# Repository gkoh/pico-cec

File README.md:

# Pico-CEC

A Raspberry Pi Pico based project to bridge HDMI CEC (Consumer Electronics
Control) and USB HID keyboard control (especially for use with Kodi).

## Update January 2026

The reference hardware for `pico-cec` has been upgraded from RP2040 to RP2350. Support for RP2040 builds will continue where possible.

## Motivation

Micro/mini desktops are plentiful as second hand, budget friendly media players,
especially when installed with Kodi (eg. LibreELEC).
However, many of these devices do not support HDMI-CEC and require the user to
use additional peripherals (eg. wireless keyboard, game controller).

In this project we use a Pico to both:
* handle the CEC protocol on the HDMI port
* adapt the user control messages into USB keyboard inputs

## What Works
* HDMI CEC frame send and receive
* EDID parsing to determine HDMI physical address
* LibreELEC recognises Pico-CEC as an USB HID keyboard
* HDMI CEC basic user control messages are properly mapped to Kodi shortcuts,
  including:
   * navigations arrows
   * select
   * back
   * play
   * pause
   * numbers 0-9
 
> [!CAUTION]
> The build quality of the HDMI breakout boards is highly variable, thus pass through of 4K video may not function in all circumstances.

## Cloning
To avoid cloning unneeded code, clone like this:
```
git -c submodule.active="lib/tinyusb" -c submodule.active=":(exclude,glob){lib,hw}/*" clone --recurse-submodules
```

Alternatively, clone everything in pico-sdk and tinyUSB:
```
git clone --recurse-submodules
```

## Building
This project uses the 'normal' CMake based build.  
The build depends on cmake (obviously), gcc-arm-none-eabi, and libnewlib-dev.

Two boards are supported, and the RP2040 and RP2350 produce incompatible
`.uf2` images, so build for the board you actually have:
```
$ git clone <blah blah as above>
$ cd pico-cec
```

For the Seeed XIAO RP2350 (current reference hardware):
```
$ cmake -S . -B build -DPICO_BOARD=seeed_xiao_rp2350 && cmake --build build
```

For the Seeed XIAO RP2040 (legacy):
```
$ cmake -S . -B build -DPICO_BOARD=seeed_xiao_rp2040 && cmake --build build
```

Switching boards requires a clean build directory (`rm -rf build`).

### Customising the Build
The CMake project supports three options:
* PICO_BOARD: specify variant of Pico board, defaults to Seeed XIAO RP2350 (potential values [here](https://github.com/raspberrypi/pico-sdk/tree/master/src/boards/include/boards))
* CEC_PIN: specify GPIO pin for HDMI CEC, defaults to GPIO3
* CEC_OSD_NAME: specify the OSD string for HDMI input Pico-CEC is controlling, defaults to "Pico-CEC"
Example invocation to specify:
* use Raspberry Pi Pico development board
* use GPIO pin 11
* use OSD_NAME "Bazzite"

```
$ cmake -DPICO_BOARD=pico -DCEC_PIN=11 -DCEC_OSD_NAME="Bazzite" ..
$ make
```

## Installing
Assuming a successful build, the build directory will contain `pico-cec.uf2`,
this can be written to the Pico as per normal:
* connect the Pico to computer via USB cable
* reset the Pico by holding 'Boot' and pressing 'Reset'
   * Pico now presents as a USB mass storage device
* copy `pico-cec.uf2` to the Pico
* disconnect

A command line interface over serial port is available, the guide can be found
here: [Command Line Interface Guide](https://github.com/gkoh/pico-cec/wiki/Command-Line-Interface-Guide)

## Blinking Lights
The RGB LED provides basic functional diagnosis:
* blue 2Hz: idle, CEC standby
* green 2Hz: CEC active
* green flash: CEC user button pressed
* red: crash

If there are no lights, something is very wrong.
If this occurs, please consider raising an issue.

# Real World Usage
This is currently working with:
* a Sharp 60" TV (physical address 0x1000)
   * directly connected to TV HDMI input 1
* through a Denon AVR connected to the Sharp TV (physical address 0x1100)
   * Pico-CEC connected to Denon AVR HDMI input 1
   * Denon AVR connected to TV HDMI input 1
* a Sony 60" TV (physical address 0x1000)
   * directly connected to TV HDMI input 1

# Design
## Hardware
The hardware connections are extremely simple. Both HDMI CEC and the Pico are
3.3V obviating the need for level shifters. The DDC bus (for EDID) is I2C and
5V, however, the Pico appears to be 5V tolerant.

Additionally, we rely on the GPIO input/output impedance states to read or drive
the CEC bus. DDC is I2C requiring data and clock lines.
Thus, we need to directly connect four wires:
* HDMI CEC pin 13 direct to a GPIO
* HDMI CEC ground pin 17 direct to GND
* HDMI DDC clock pin 15 direct to SCL
* HDMI DDC data pin 16 direct to SDA
* Optional if safe:
   * HDMI +5V power pin direct to 5V

For the Seeed Studio XIAO RP2350:
* HDMI pin 13 --> D10
* HDMI pin 17 --> GND
* HDMI pin 15 --> D5
* HDMI pin 16 --> D4
* HDMI pin 18 --> 5V/VUSB

### Schematic

After this we:
* connect `Pico-CEC` to the HDMI output of the PC
* connect the HDMI cable from the TV to `Pico-CEC`
* connect a USB cable from `Pico-CEC` to the PC

### Prototype

### Enclosure
The enclosure is a reasonably simple three piece sandwich 3d print modelled with OpenSCAD. It is designed to be printed as three separate pieces which are bolted together with M3 nuts and bolts.
An exploded preview of the result can be found in this [STL](openscad/pico-cec.stl).

### PCB

The hardware is split across two KiCad projects under [`pcb/`](pcb). You will
need to have *both* these boards produced:

* [`pcb/hdmi-breakout`](pcb/hdmi-breakout) — the HDMI passthrough breakout that
  carries the CEC and DDC signals. This is a 4-layer board; order it with the
  **JLC04161H-7628 stackup**. Stackup is not a minor detail; incorrect stackup
  will destroy performance.
* [`pcb/rp2040-adaptor`](pcb/rp2040-adaptor) — a simple breakout for the RP2040-Zero
  that connects to the HDMI breakout. This is an ordinary **2-layer** board with
  no controlled-impedance requirement, so any standard stackup is fine.

Shared symbols and footprints live in [`pcb/library`](pcb/library). Fabrication
outputs (gerbers, BOM, CPL) for each board can be generated with
[`jlcpcb_fab.py`](jlcpcb_fab.py).

Additional BOM (parts to source separately on top of the fabricated boards):

| Count | Part |
| ----- | ---- |
| 2 | HDMI Type-A receptacle (Molex 208658-1001, LCSC C138388) |
| 1 | Waveshare RP2040-Zero |
| 2 | 1×9 2.54mm male pin header strip |
| 2 | 1×9 2.54mm female header / socket strip |
| 2 | M3 × 16mm socket head cap screw |
| 2 | M3 nut |

Remember that you can easily cut a longer 2.54mm header to size with some snips.

### Assembly

## Software
The software is extremely simple and built on FreeRTOS tasks:
* cec_task
   * interact with HDMI CEC sending user control message inputs to a queue
* hid_task
   * read the user control messages from the queue and send to the USB task
* usbd_task
   * generate an HID keyboard input for the USB host
* blink_task
   * heart beat, no blink == no work

## cec_task
The CEC task comprises three major components:
* `cec_frame_recv`
   * receives and validates CEC packets from the CEC GPIO pin
   * edge interrupt driven state machine
      * rewritten from busy wait loop to reduce CPU load
* `cec_frame_send`
   * formats and sends CEC packets on the CEC GPIO pin
   * alarm interrupt driven state machine
      * rewritten from busy wait loop to reduce CPU load
* main control loop
   * manages CEC send and receive

All the HDMI frame handling was rewritten to be hardware/timer interrupt driven
to meet real-time constraints.
Attempts to increase the FreeRTOS tick timer along with busy wait loops were
simply unable to consistently meet the CEC timing windows.

## hid_task and usbd_task

These are simple FreeRTOS tasks effectively taken straight from the TinyUSB
examples.

## Dependencies
This project uses:
* [crc](https://github.com/gityf/crc)
* [FreeRTOS-Kernel](https://github.com/FreeRTOS/FreeRTOS-Kernel)
* [pico-sdk](https://github.com/raspberrypi/pico-sdk)
   * [tinyusb](https://github.com/hathach/tinyusb)
* [tcli](https://github.com/dpse/tcli)

# Hardware
* Seeed Studio XIAO RP2350 (chosen for form factor)
   * https://www.seeedstudio.com/Seeed-XIAO-RP2350-p-5944.html
   * Originally prototyped on the Raspberry Pi Pico board (still works but
     requires RGB unhacking)
* HDMI male/female passthrough adapter
   * Listed as 'HDMI Male and Female Test Board MINI Connector with Board PCB
     2.54mm pitch 19/20pin DP HD A Female To Male Adapter Board'
   * Model number: WP-905
   * https://www.aliexpress.com/item/1005004791079117.html
* custom 3d printed housing

# Bill of Materials
| Component | Quantity | Price (January 2026) (AUD) |
| :--- | ---: | ---: |
| Seeed Studio XIAO RP2350 | 1 | 10.60 |
| HDMI male/female adapter | 1 | 4.30 |
| M3x10mm bolt & nut | 2 | 0.16 |
| M3x20mm bolt & nut | 2 | 0.17 |
| Random short wires | 4 | basically free |
| Scunge 3D print from friend | 1 | mostly free |
| Umpteen hours of engineering | 1 | priceless |
| Total | | 15.23 |

# cec-compliance
As of v0.2.2, `pico-cec` now passes the cec-compliance test suite found in the
Linux `v4l-utils` package.
More details can be found in the wiki entry:
https://github.com/gkoh/pico-cec/wiki/CEC-Compliance-Testing

Furthermore, `pico-cec` has been able to survive one hour of cec-compliance fuzz
testing.

# Debugging
A command line terminal over serial port is supported.
Details can be found in the wiki entry:
https://github.com/gkoh/pico-cec/wiki/Command-Line-Interface-Guide

In particular, `debug on` will log all CEC traffic to the terminal.

# Future
* implement CEC send and receive in PIO
* port to ESP32?
   * WS2812 driver will need platform support, perhaps to RMT
   * implement CEC in RMT

# References
Inspiration and/or ground work was obtained from the following:
* https://github.com/SzymonSlupik/CEC-Tiny-Pro
* https://github.com/tsowell/avr-hdmi-cec-volume

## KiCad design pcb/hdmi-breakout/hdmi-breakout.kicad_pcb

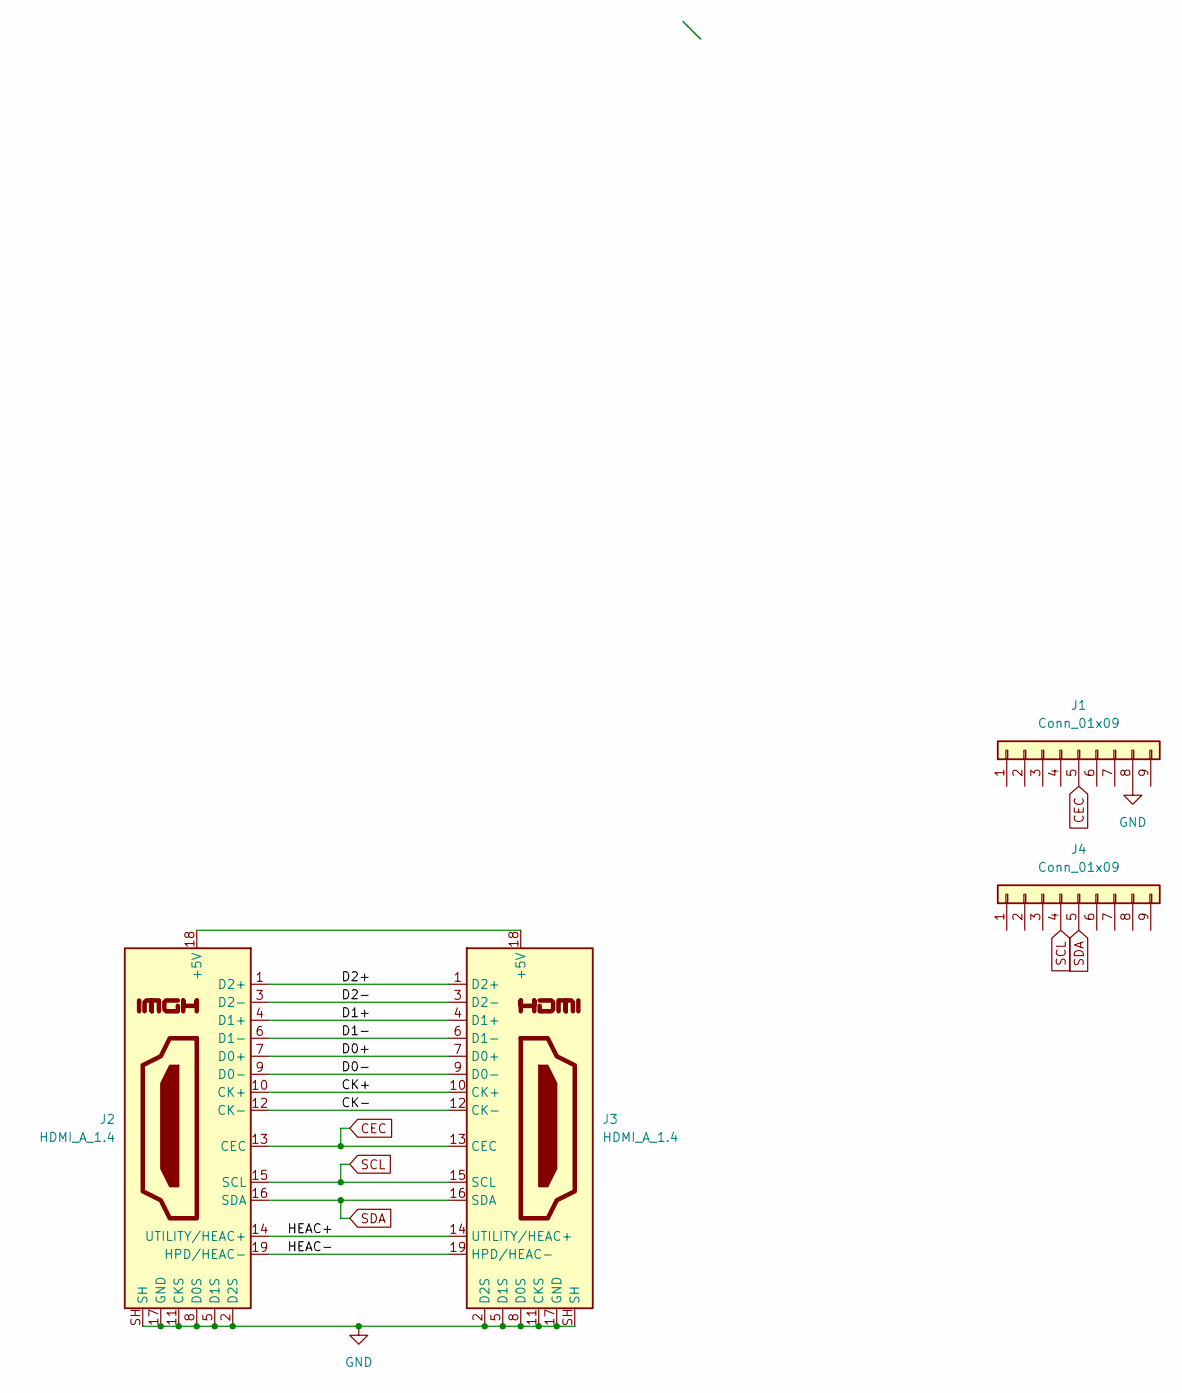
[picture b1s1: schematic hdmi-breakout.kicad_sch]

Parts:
J1, J4: Conn_01x09; PinHeader_1x09_P2.54mm_Vertical
J2, J3: HDMI_A_1.4; HDMI_A_Molex_208658-1001_Horizontal; LCSC C138388

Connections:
/CK+: J2.10 (CK+), J3.10 (CK+)
/CK-: J2.12 (CK-), J3.12 (CK-)
/D0+: J2.7 (D0+), J3.7 (D0+)
/D0-: J2.9 (D0-), J3.9 (D0-)
/D1+: J2.4 (D1+), J3.4 (D1+)
/D1-: J2.6 (D1-), J3.6 (D1-)
/D2+: J2.1 (D2+), J3.1 (D2+)
/D2-: J2.3 (D2-), J3.3 (D2-)
/HEAC+: J2.14 (UTILITY/HEAC+), J3.14 (UTILITY/HEAC+)
/HEAC-: J2.19 (HPD/HEAC-), J3.19 (HPD/HEAC-)
CEC: J1.5, J2.13 (CEC), J3.13 (CEC)
GND: J1.8, J2.2 (D2S), J2.5 (D1S), J2.8 (D0S), J2.11 (CKS), J2.17 (GND), J2.SH, J3.2 (D2S), J3.5 (D1S), J3.8 (D0S), J3.11 (CKS), J3.17 (GND), J3.SH
unnamed: J2.18 (+5V), J3.18 (+5V)
SCL: J2.15 (SCL), J3.15 (SCL), J4.4
SDA: J2.16 (SDA), J3.16 (SDA), J4.5

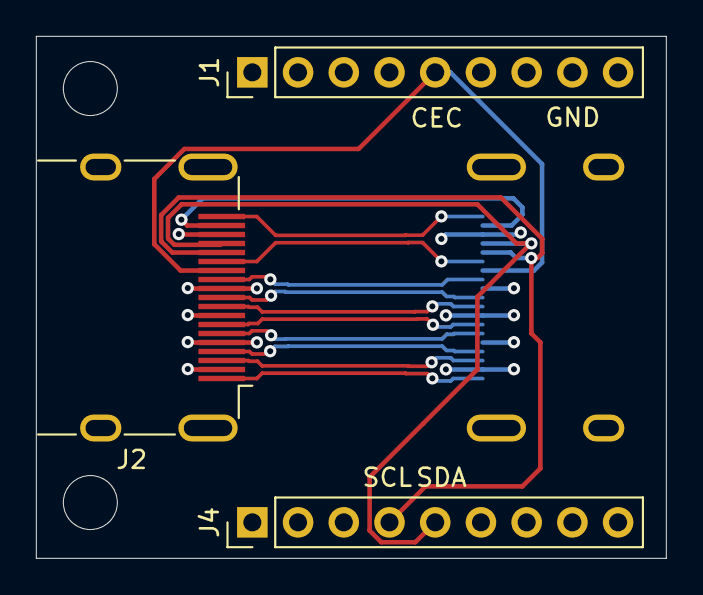
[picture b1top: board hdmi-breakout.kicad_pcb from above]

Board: 4 copper layers, 35.0 x 29.0 mm, 4 parts (1 on the bottom side), 15 nets.

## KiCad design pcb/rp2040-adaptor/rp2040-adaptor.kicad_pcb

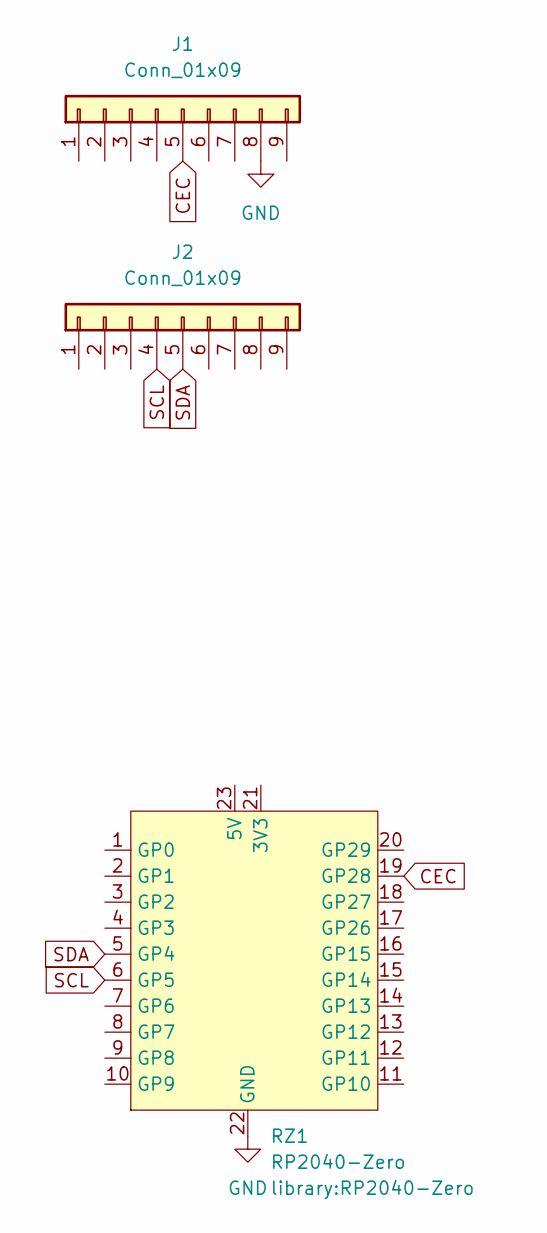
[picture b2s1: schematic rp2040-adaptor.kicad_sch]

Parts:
J1, J2: Conn_01x09; PinSocket_1x09_P2.54mm_Vertical
RZ1: RP2040-Zero

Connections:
CEC: J1.5, RZ1.19 (GP28)
GND: J1.8, RZ1.22 (GND)
SCL: J2.4, RZ1.6 (GP5)
SDA: J2.5, RZ1.5 (GP4)

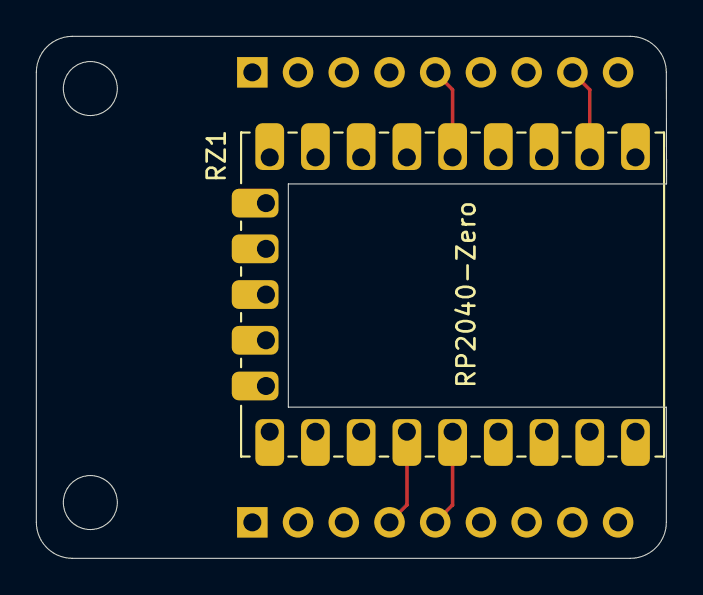
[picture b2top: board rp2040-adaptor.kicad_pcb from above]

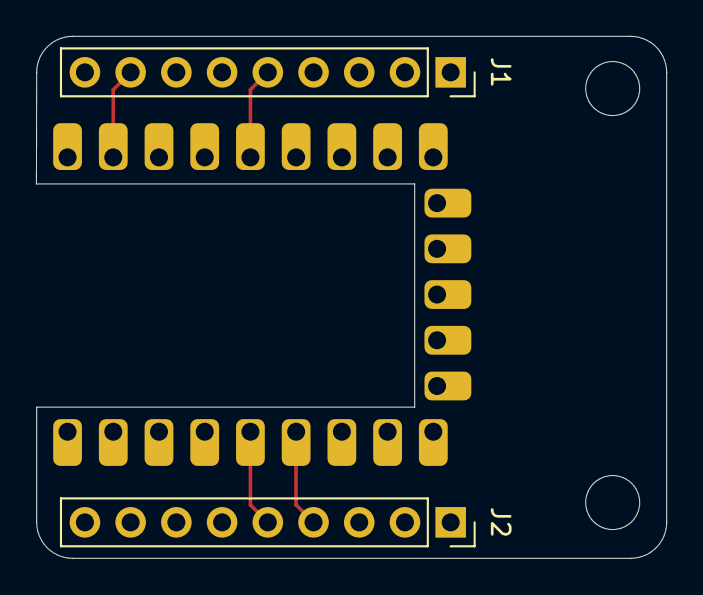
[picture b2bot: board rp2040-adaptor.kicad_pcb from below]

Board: 2 copper layers, 35.0 x 29.0 mm, 3 parts (2 on the bottom side), 4 nets.

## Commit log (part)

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2024-05-28 Initial commit.
2024-06-01 Fix stack sizes for tasks.
    FreeRTOS stack sizes are specified as words (default 4 bytes for
    rp2040).
    This may have been the cause of the intermittent hangs.
2024-06-04 Another attempt to avoid random hang.
    Tweak stack sizes again.
    Give usbd all 4k stack on core 1.
    Move HID to core 0.
    Disable copy_to_ram for now.
2024-06-07 Tweak various parameters.
    Send notify on abort (otherwise aborted CEC messages hang the system).
    Add necessary PICO_SYNC definitons to ensure FreeRTOS compatibility.
    This version seems to have fixed the various hangs.
    (Retweak the stack sizes based on high water mark values).
2024-06-10 Tweak 3d model after prototype print.
    Increase various tolerances and add LED visibility.
    Also fix dependency in Makefile.
2024-06-10 Freeze FreeRTOS-Kernel at V11.1.0.
    pico-sdk is already frozen at 1.5.1.
2024-06-16 Further cleanup of CMake project file.
2024-06-19 Initial cut of README.
2024-06-19 Tweak case tolerances.
    Increase M3 nut radius.
    Increase M3 bolt radius.
    Increase HDMI male width.
2024-06-19 Add build directory to gitignore.
2024-06-23 Add clang-format check to CI.
    Add recursive submodule checkout fix.
2024-06-23 Fix more silly mistakes.
2024-06-23 Add submodule init & update for tinyusb.
2024-06-23 Add anonymous scope to fix declaration compiler error.
    Seems an older version of GCC and/or C standard doesn't like it.
2024-06-23 Add STL export step to CI.
2024-06-23 Add required runs-on.
2024-06-23 Flatten the download-artifact assets.
2024-06-23 Give release job write permission to upload assets.
2024-07-01 Fix README.md table.
2024-07-03 Adjust semi-exploded for piece clarity.
2024-07-03 Fix typo.
2024-07-21 Implement logical address allocation for playback addresses.
    With an array of the playback addresses, ping each one in order to
    discover which is free.
    Whilst here, implement the CEC version reply (and reply with 1.3a).
2024-07-22 Update real-world usage in README.
2024-07-25 Implement EDID parsing to query physical address.
    Add I2C support for the HDMI DDC bus and query the upstream device for
    our HDMI physical address.
    This means the physical address is no longer hardcoded.
    Tested working with the following upstream devices:
    * Sharp TV
    * Sony TV
2024-07-27 Clean up FreeRTOS config header.
2024-07-28 Refactor for CEC message handling.
2024-07-28 Issue a reset before reading.
    Looks like we should reset the DDC/EDID state before attempting a read.
    Do this by writing a 0 to the EDID address before trying to read any
    data back.
2024-07-28 Fix support for Samsung TV. (#6)
    * Clean up FreeRTOS config header.
    * Add debug target.
    The debug target removes the USB HID binding and allows the Pico to send
    serial output to USB.
    NB. This build output tends to hang randomly, a lot, use at risk.
    * Refactor for CEC message handling.
2024-07-29 Update schematic.
    Correct the schematic wiring pin for CEC.
2024-08-10 Add future point to README
    Perhaps port to ESP32?
    Would only really need to refactor the HDMI tx/rx interrupt/timer handling.
    Everything else is reasonably hardware agnostic.
2024-08-18 Added mappings for subtitle and context menu. (#10)
    * Added mappings for subtitle and context menu.
    * Run clang-format.
    ---------
2024-09-09 Correct workflow variable substitution.
    Also remove stale include path.
2024-09-10 Initial support for USB composite device HID and CDC. (#13)
    * Initial support for USB composite device HID and CDC.
    Enable CDC so Pico-CEC appears as a connectable serial TTY device with
    baud rate 115200.
    Add tcli v0.2.5 as submodule.
    Add basic example CLI support via tcli for:
    * reboot [bootsel]
2025-02-15 Stop installing recommended packages for CI.
    Seriously, we don't need all that.
2025-02-15 Add another missing package.
2025-02-15 Add non-volatile configuration parameters.
    Increase NVS block to 64kB.
    Import CRC library.
    Add default EDID probe delay.
    Add default physical address (0x0000 means EDID probe).
    Add default Kodi keymap.
2025-02-19 Add delay to avoid serial output lock.
    Serial still causes full system hang sometimes, but this seems to make
    it occur far less often.
2025-02-19 Add link to CLI wiki.
2025-02-19 Disable SMP.
    CPU stats indicate pico-cec idles both cores almost 100% of the time.
    This means CPU requirements are insanely low, as expected.
    Now we just mostly idle a single core.
    This is also seems to completely eliminate the serial deadlock
    behaviour.
    (Updating to pico-sdk v2.1.1 did not fix it).
2025-02-22 Pass cec-compliance `--test-core`.
2025-02-22 Pass cec-compliance routing test.
2025-02-23 Improve some debug output traces.
    Condense the EDID query block logging by printing 8 bytes at a time.
    Modify the CEC message direction log such that:
    * "x -> y" = x sent to y with ack
    * "x <- y" = y sent to x with ack
    * "x ~> y" = x sent to y no ack
    * "x <~ y" = y sent to x no ack
2025-02-26 Properly support default keymap upgrades.
    Implement NVS version detection and migration.
    Add a 'keymap_type' field for identification of keymaps.
    Add currently unused 'logical address' configuration.
    Add keymap for MiSTer and provide build time support to enable.
    Refactor keymap handling.
    Add 'show nvs' command to display basic NVS configuration.
2025-02-26 Add unused device type.
2025-02-27 Fix build for boards with no user LED.
    Update README to clarify Pico dev board support.
2025-02-28 Fix user control message handling.
    Ensure that pico-cec only responds to user control messages destined for
    its logical address.
    Prior to this fix, pico-cec would respond to _all_ user control messages
    on the CEC bus, regardless of destination device.
2025-02-28 Add github run-id to artifact reference.
2025-02-28 Add some missing undecoded CEC message IDs.
2025-03-03 Improve active source handling.
    If `Request Active Source` is received three times without a response
    from any other device, become the active source.
2025-03-04 Update README.md
    Correct the wire count in the BOM.
    Add more future things.
2025-06-13 Improve code portability
    Minor additions/modifications required to existing code-base for compatibility with espressif esp32 compiler.
2025-06-15 Added console support on secondary UART
    The secondary esp32 uart is configured for the tcli console, with the primary uart still utilised for diagnostics.
2025-06-17 rename a couple of port support modules
    In order to improve namespace clarity utilised git mv to change name of a couple of port support modules.
2025-06-18 Update hdmi-cec-link.h
    Remove draft commit summary from source file.
2025-06-19 Correct header inclusion for 'memset()'.
2025-06-19 Update hdmi-cec-link.c
    Fix a missed clang-format violation.
2025-06-23 esp32 target now sends and receives cec messages
    Significant progress along with major cleanup of the port code.
    Also successfully build tested the pico target. Requires replacing CMakeFiles.txt with the accompanying CMakeFiles.pico
    More work to come with renaming a few modules as discussed in the refactoring pull request.
2025-06-24 Further fix-ups to previous commit
    Mostly to quiet the format checker, but a few fixes addressing issues found during an independent build test.
2025-06-24 Exclude `lib` from clang-format.
2025-06-26 Add i2c support and improve trace capability
    Both the legacy and new esp-idf i2c driver models are optionally supported. The former requires no change to the mainline source, the later requires a single processor conditional.
2025-07-01 Rename select modules and numerous update candidates
    Significant cleanup preparing for a merge candidate.
    As yet no run-time test conducted on pico hardware.
    Proposed solution to disparate requirements for CMakeLists.txt is to require the user to copy one of the template versions as provided.
    Now includes I2C (DDC) support, with options to try both new and legacy esp-idf i2c drivers.
    Two potential methods to facilitate pico-sdk header inclusion - either with dummy (empty) headers in a replicated directory structure (to satisfy the C pre-processor), or by including all required he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
2025-07-01 Appease clang-format
2025-07-06 progress towards decoupling cec and cdc functionality, et-al
    decouple cec user control name strings from both config and log modules
    - allows cec-log to exist independent of the application configuration (cec-config) functionality
    - cec-log could readily be minimised to not support higher level cec user control specific support
    - cec-config need know nothing else about the cec logging capability (this may warrant a re-think)
    - cec-config just needs access to a string table which it doesn't make sense to own
    move and rename function cec_get_uptime_ms() to cec_log_uptime_ms()
2025-07-13 Refactor _CDC_BR handling.
    Add _LOG_BR macro for _CDC_BR to streamline header inclusion.
    Any modules requiring logging need only include `cec-log.h`.
2025-07-18 Update cec-log.h
    Attempt to address the failing GitHub automated build tests.
2025-07-18 Isolate pico-sdk specific header files
    Isolation of pico-sdk only include files from architecture independent common source modules is required to support ports to other devices.
2025-07-24 Update on esp32 port progress
    Builds and runs nicely on both esp32 and pico-pi.
    With the addition of several new diagnostic features, RX_ABORTS have seemingly been eliminated.
    Additional feature allows asynchronous sending of cec messages from external tasks.
2025-07-24 Grin and bear the frustration that is Git
2025-08-19 Progress update
2025-08-19 Address the format checker issue
2025-12-26 Add CEC-Enabler board definiton from LaserBearIndustries/CEC_Enabler sources.
    CEC-Enabler is based on the Waveshare RP2040-Zero.
2026-01-21 Menu status logic reversed + detailed log
2026-01-22 Implement CEC menu request handling.
    Track menu state and respond to menu request message.
    Use this to enhance the overall menu status handling.
    Pico-CEC still passes CEC compliance and now supports the menu test.
2026-01-22 Add seeed-xiao-rp2350 to build workflow.
    Whilst here, correct the build matrix to actually build the target
    specified.
2026-01-29 Chamfer the sharp edges and corners.
    Add the BOSL2 library and chamfer for a less pointy aesthetic.
2026-01-30 Update release workflow for both Seeed XIAO Pico boards.
2026-01-30 Actually add uf2 binaries to release zip.
2026-02-02 Update apt repository before installing packages.
2026-04-13 Add a 'send' CLI command.
    This allows me to turn on/off my TV by with a UART command.
    Examples:
    - send 4: set image view on (turn TV on)
    - send 36: set standby (turn TV off)
2026-04-17 Directly address TV with send command.
    Use our logical address and use the TV's direct address for send
    commands.
2026-04-19 Add CLI support for custom keymaps.
    Add new 'set' command with format:
    set keymap custom <cec> <hid>
    where '<cec>' is the CEC user control code in hexadecimal and '<hid>' is
    the HID key code in hexadecimal.
2026-05-04 Fix CEC_PIN customisation.
    This has been broken since the refactor.
    The source compile rule was targeting the wrong source file.
    Fixes: 9c4f6b497fd5 ("Minor refactor")
2026-05-16 Document RP2040/RP2350 board builds in README
    Add separate build commands for the Seeed XIAO RP2350 and RP2040, and
    note that the two produce incompatible .uf2 images. Use the short-form
    cmake -S/-B invocation.
2026-05-20 Add caution about 4K support
    Update README for possible lack of 4K support due to HDMI breakout build quality
2026-06-06 add preview, fix bugs
